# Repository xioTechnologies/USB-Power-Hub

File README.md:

USB-Power-Hub
=============

A USB power hub for powering up to 13 or 26 USB devices from a benchtop power supply.  Bill of materials:
* [USB Female Type A SMD Connector](https://www.sparkfun.com/products/9011) (x13)
* [Binding Post - Red](https://www.sparkfun.com/products/9739)
* [Binding Post - Black](https://www.sparkfun.com/products/9740)
* Resistor
* 5mm LED

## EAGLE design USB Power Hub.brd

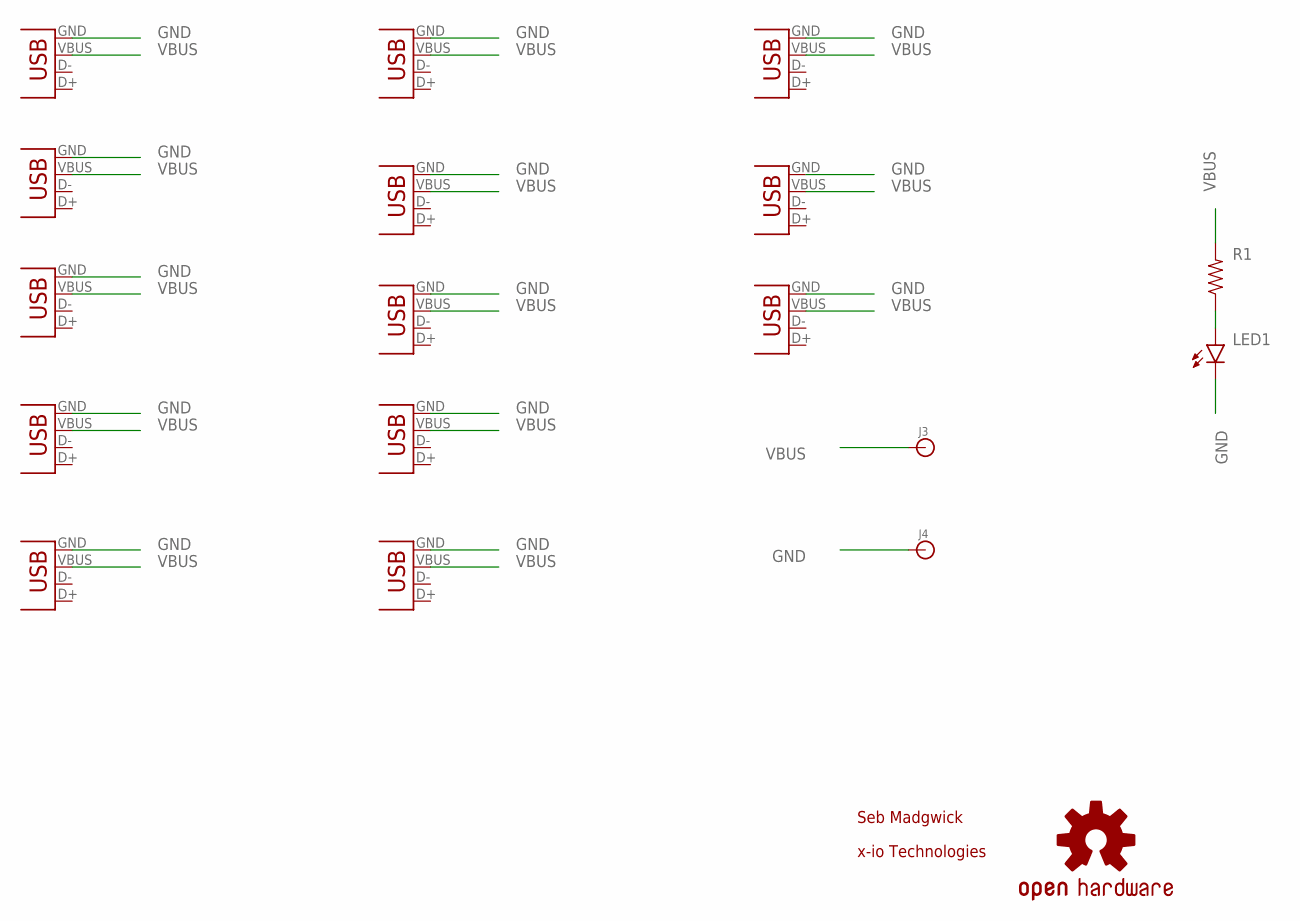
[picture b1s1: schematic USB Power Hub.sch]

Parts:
J3, J4: BANANA_CONN
JP1, JP2, JP3, JP4, JP5, JP6, JP7, JP8, JP9, JP10, JP11, JP12, JP13: USB-A-S
LED1: LED5MM
LOGO1: OSHW-LOGOL; OSHW-LOGO-L
R1: RESISTOREZ; AXIAL-0.3EZ

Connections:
GND: J4.P$1, JP1.GND, JP2.GND, JP3.GND, JP4.GND, JP5.GND, JP6.GND, JP7.GND, JP8.GND, JP9.GND, JP10.GND, JP11.GND, JP12.GND, JP13.GND, LED1.K (C)
unnamed: LED1.A, R1.P$1 (1)
VBUS: J3.P$1, JP1.VBUS, JP2.VBUS, JP3.VBUS, JP4.VBUS, JP5.VBUS, JP6.VBUS, JP7.VBUS, JP8.VBUS, JP9.VBUS, JP10.VBUS, JP11.VBUS, JP12.VBUS, JP13.VBUS, R1.P$2 (2)

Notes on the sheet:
Seb Madgwick
x-io Technologies

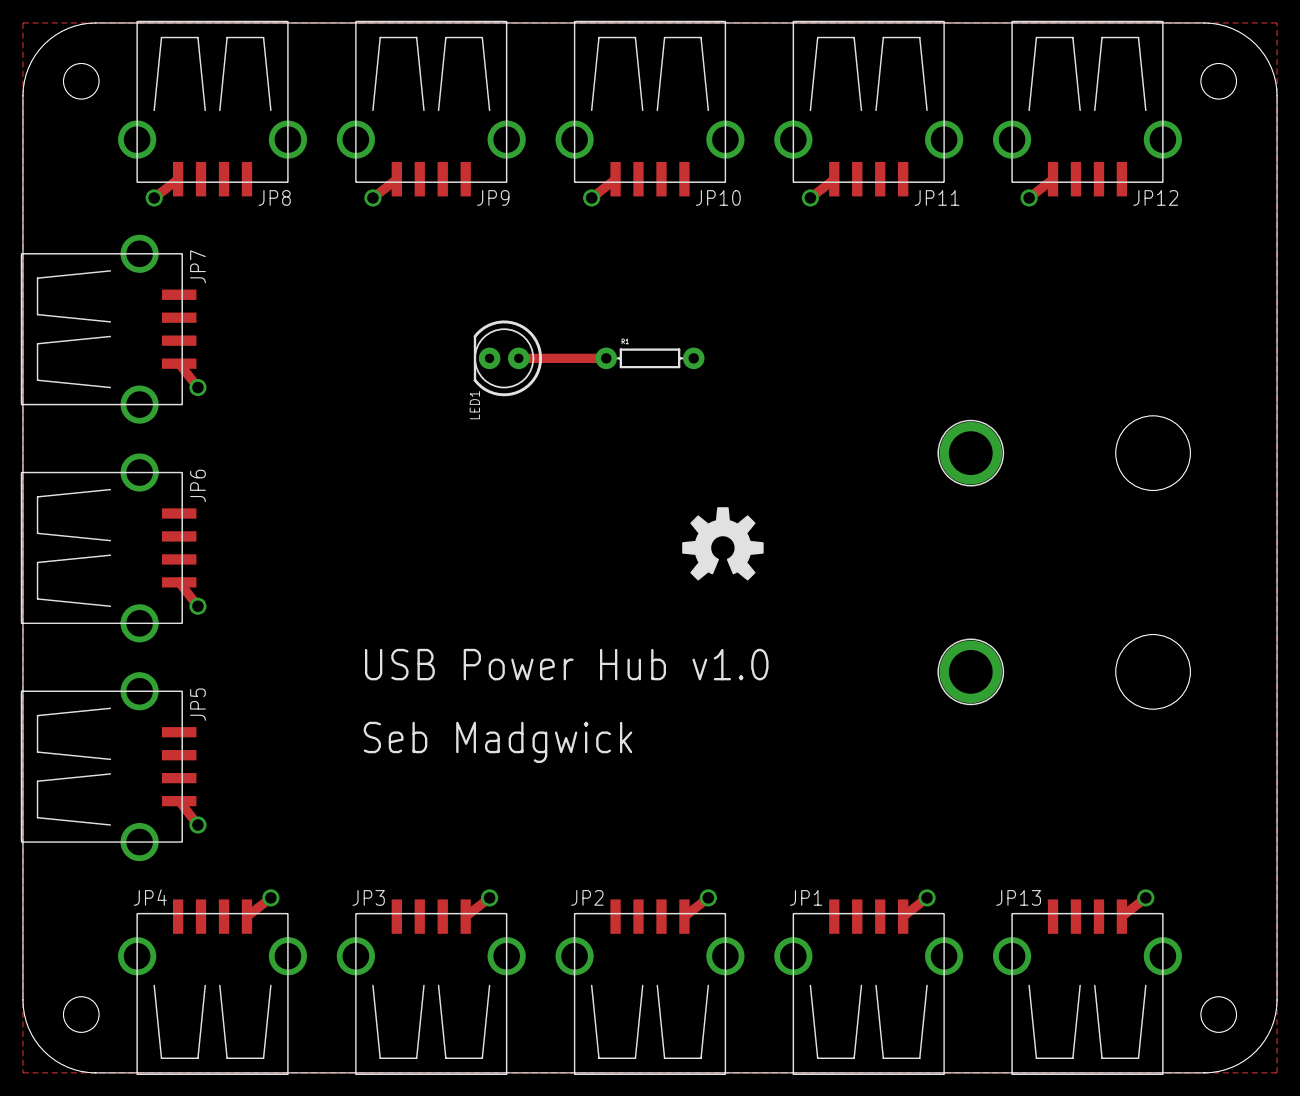
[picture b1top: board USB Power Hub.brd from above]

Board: 2 copper layers, 109.2 x 91.4 mm, 19 parts (0 on the bottom side), 3 nets.

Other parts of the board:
U$2: X-IO_TECHNOLOGIES_LOGO_20MM_TOP

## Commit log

2014-07-18 Commit project files
2014-08-06 Add photos

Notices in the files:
parts and their libraries:
SparkFun-LED: Licensing: Creative Commons ShareAlike 4.0 International - https://creativecommons.org/licenses/by-sa/4.0
